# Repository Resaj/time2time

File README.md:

# time2time

Chronometer with partials measurement for the line-following competitions.

Characteristics:
- ESP32 module (STM microcontroller + Bluetooth + Wifi)
- Industrial distance sensor for robots pass-through detection
- Lipo 1S battery
- USB Lipo battery charge management
- I2C OLED display port
- Buzzer for robots pass-through signaling
- RGB led for chronometer status signaling
- Firmware upload via USB
- Address selection to synchronize several modules
- Expansion port for future improvements

This project has been motivated because of the limitations that the last chronometer had. The main purpose is to communicate the system with the PC of the competition organization and facilitate the taking and visualization of the times.

## Author

[Rubén Espino San José](https://github.com/Resaj)

## License

_All these products are released under [Creative Commons Attribution-NonCommercial-ShareAlike 4.0 International License](http://creativecommons.org/licenses/by-nc-sa/4.0/)._

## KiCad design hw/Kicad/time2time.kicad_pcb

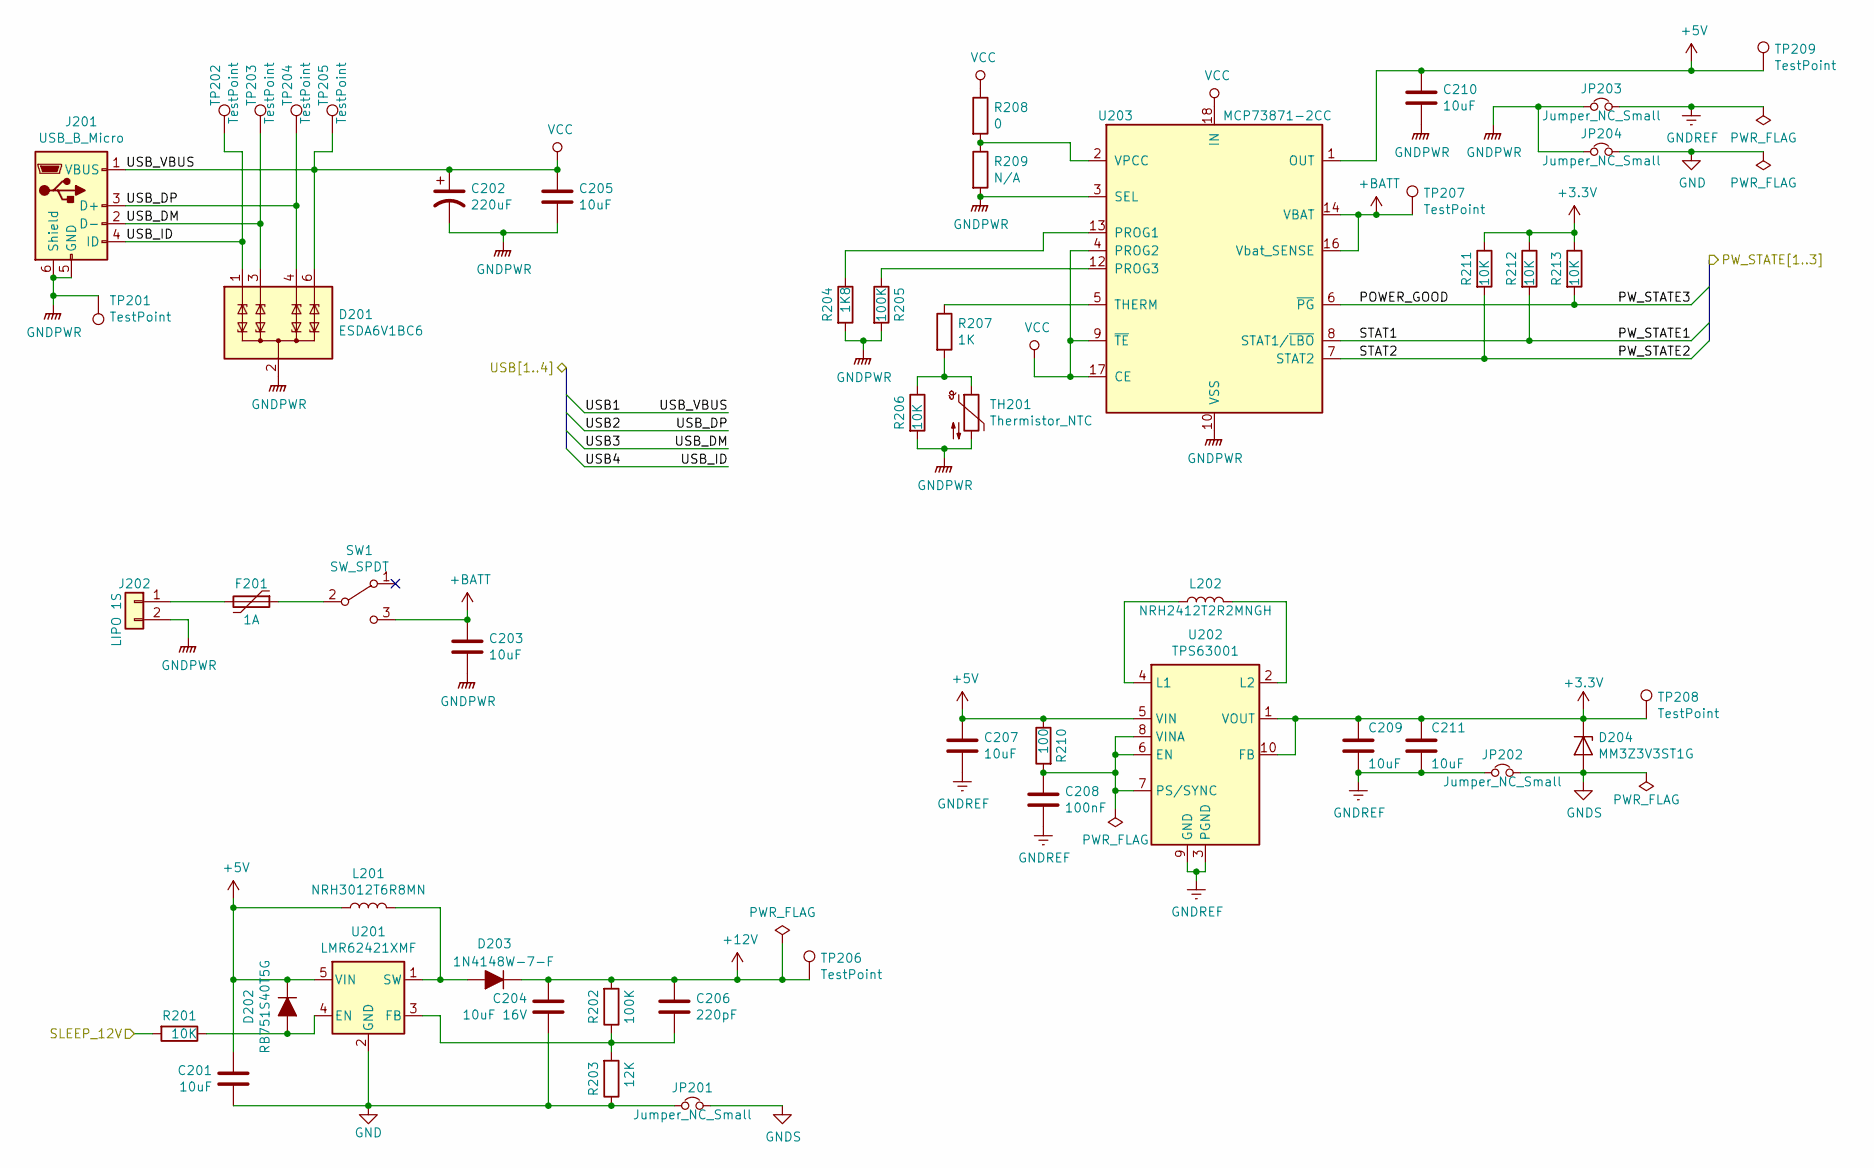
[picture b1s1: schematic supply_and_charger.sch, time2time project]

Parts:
C201, C203, C205, C207, C209, C210, C211: 10uF; C_0603_1608Metric
C202: 220uF; CP_Radial_D6.3mm_P2.50mm
C204: 10uF 16V; C_0603_1608Metric
C206: 220pF; C_0603_1608Metric
C208: 100nF; C_0603_1608Metric
D201: ESDA6V1BC6; SOT-23-6
D202: RB751S40T5G; D_SOD-523
D203: 1N4148W-7-F; D_SOD-123
D204: MM3Z3V3ST1G; D_SOD-323_HandSoldering
F201: 1A; Fuse_1812_4532Metric
J201: USB_B_Micro; USB_Micro-B_Molex-105017-0001
J202: LIPO 1S; JST_PH_B2B-PH-K_1x02_P2.00mm_Vertical
JP201, JP202, JP203, JP204: Jumper_NC_Small; SolderJumper-2_P1.3mm_Bridged_Pad1.0x1.5mm
L201: NRH3012T6R8MN; L_Taiyo-Yuden_NR-30xx_HandSoldering
L202: NRH2412T2R2MNGH; L_Taiyo-Yuden_NR-24xx_HandSoldering
R201, R206, R211, R212, R213: 10K; R_0603_1608Metric
R202, R205: 100K; R_0603_1608Metric
R203: 12K; R_0603_1608Metric
R204: 1K8; R_0603_1608Metric
R207: 1K; R_0603_1608Metric
R208: 0; R_0603_1608Metric
R209: N/A; R_0603_1608Metric
R210: 100; R_0603_1608Metric
SW1: SW_SPDT; SW_CuK_OS102011MA1QN1_SPDT_Angled
TH201: Thermistor_NTC; PinHeader_1x02_P2.54mm_Vertical
TP201, TP202, TP203, TP204, TP205, TP206, TP207, TP208, TP209: TestPoint; TestPoint_Pad_D1.5mm
U201: LMR62421XMF; SOT-23-5
U202: TPS63001; Texas_DRC0010J_ThermalVias
U203: MCP73871-2CC; QFN-20-1EP_4x4mm_P0.5mm_EP2.5x2.5mm

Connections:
+5V: C201.2, C207.1, C210.1, D202.1 (K), L201.1, R210.1, TP209.1, U201.5 (VIN), U202.5 (VIN), U203.1 (OUT), U203.20 (OUT); also elsewhere on the board
+12V: C204.2, C206.1, D203.1 (K), R202.2, TP206.1; also elsewhere on the board
+BATT: C203.1, SW1.3 (C), TP207.1, U203.14 (VBAT), U203.15 (VBAT), U203.16 (Vbat_SENSE); also elsewhere on the board
/microcontroller/PW_STATE1: R212.2, U203.8 (STAT1/~LBO~); also elsewhere on the board
/microcontroller/PW_STATE2: R211.2, U203.7 (STAT2); also elsewhere on the board
/microcontroller/SLEEP_12V: R201.2; also elsewhere on the board
/microcontroller/USB2: D201.4 (TVS3), J201.3 (D+), TP204.1; also elsewhere on the board
/microcontroller/USB3: D201.3 (TVS2), J201.2 (D-), TP203.1; also elsewhere on the board
/microcontroller/USB4: D201.1 (TVS1), J201.4 (ID), TP202.1
/supply & charger/POWER_GOOD: R213.2, U203.6 (~PG~); also elsewhere on the board
GND: C201.1, C204.1, JP201.1, JP204.2, R203.1, U201.2 (GND)
GNDPWR: C202.2, C203.2, C205.2, C210.2, D201.2 (COM), D201.5 (COM), J201.5 (GND), J201.6 (Shield), J202.2, JP203.1, JP204.1, R204.2, R205.2, R206.2, R209.2, TH201.2, TP201.1, U203.3 (SEL), U203.10 (VSS), U203.11 (VSS), U203.21 (VSS); also elsewhere on the board
GNDREF: C207.2, C208.2, C209.2, C211.2, JP202.1, JP203.2, U202.3 (PGND), U202.9 (GND), U202.11 (PGND)
GNDS: D204.2 (A), JP201.2, JP202.2; also elsewhere on the board
unnamed: C206.2, R202.1, R203.2, U201.3 (FB)
unnamed: C208.1, R210.2, U202.6 (EN), U202.7 (PS/SYNC), U202.8 (VINA)
unnamed: D202.2 (A), R201.1, U201.4 (EN)
unnamed: D203.2 (A), L201.2, U201.1 (SW)
unnamed: F201.1, SW1.2 (B)
unnamed: F201.2, J202.1
unnamed: L202.1, U202.4 (L1)
unnamed: L202.2, U202.2 (L2)
unnamed: R204.1, U203.13 (PROG1)
unnamed: R205.1, U203.12 (PROG3)
unnamed: R206.1, R207.2, TH201.1
unnamed: R207.1, U203.5 (THERM)
unnamed: R208.2, R209.1, U203.2 (VPCC)
VCC: C202.1, C205.1, D201.6 (TVS4), J201.1 (VBUS), R208.1, TP205.1, U203.4 (PROG2), U203.9 (~TE), U203.17 (CE), U203.18 (IN), U203.19 (IN); also elsewhere on the board

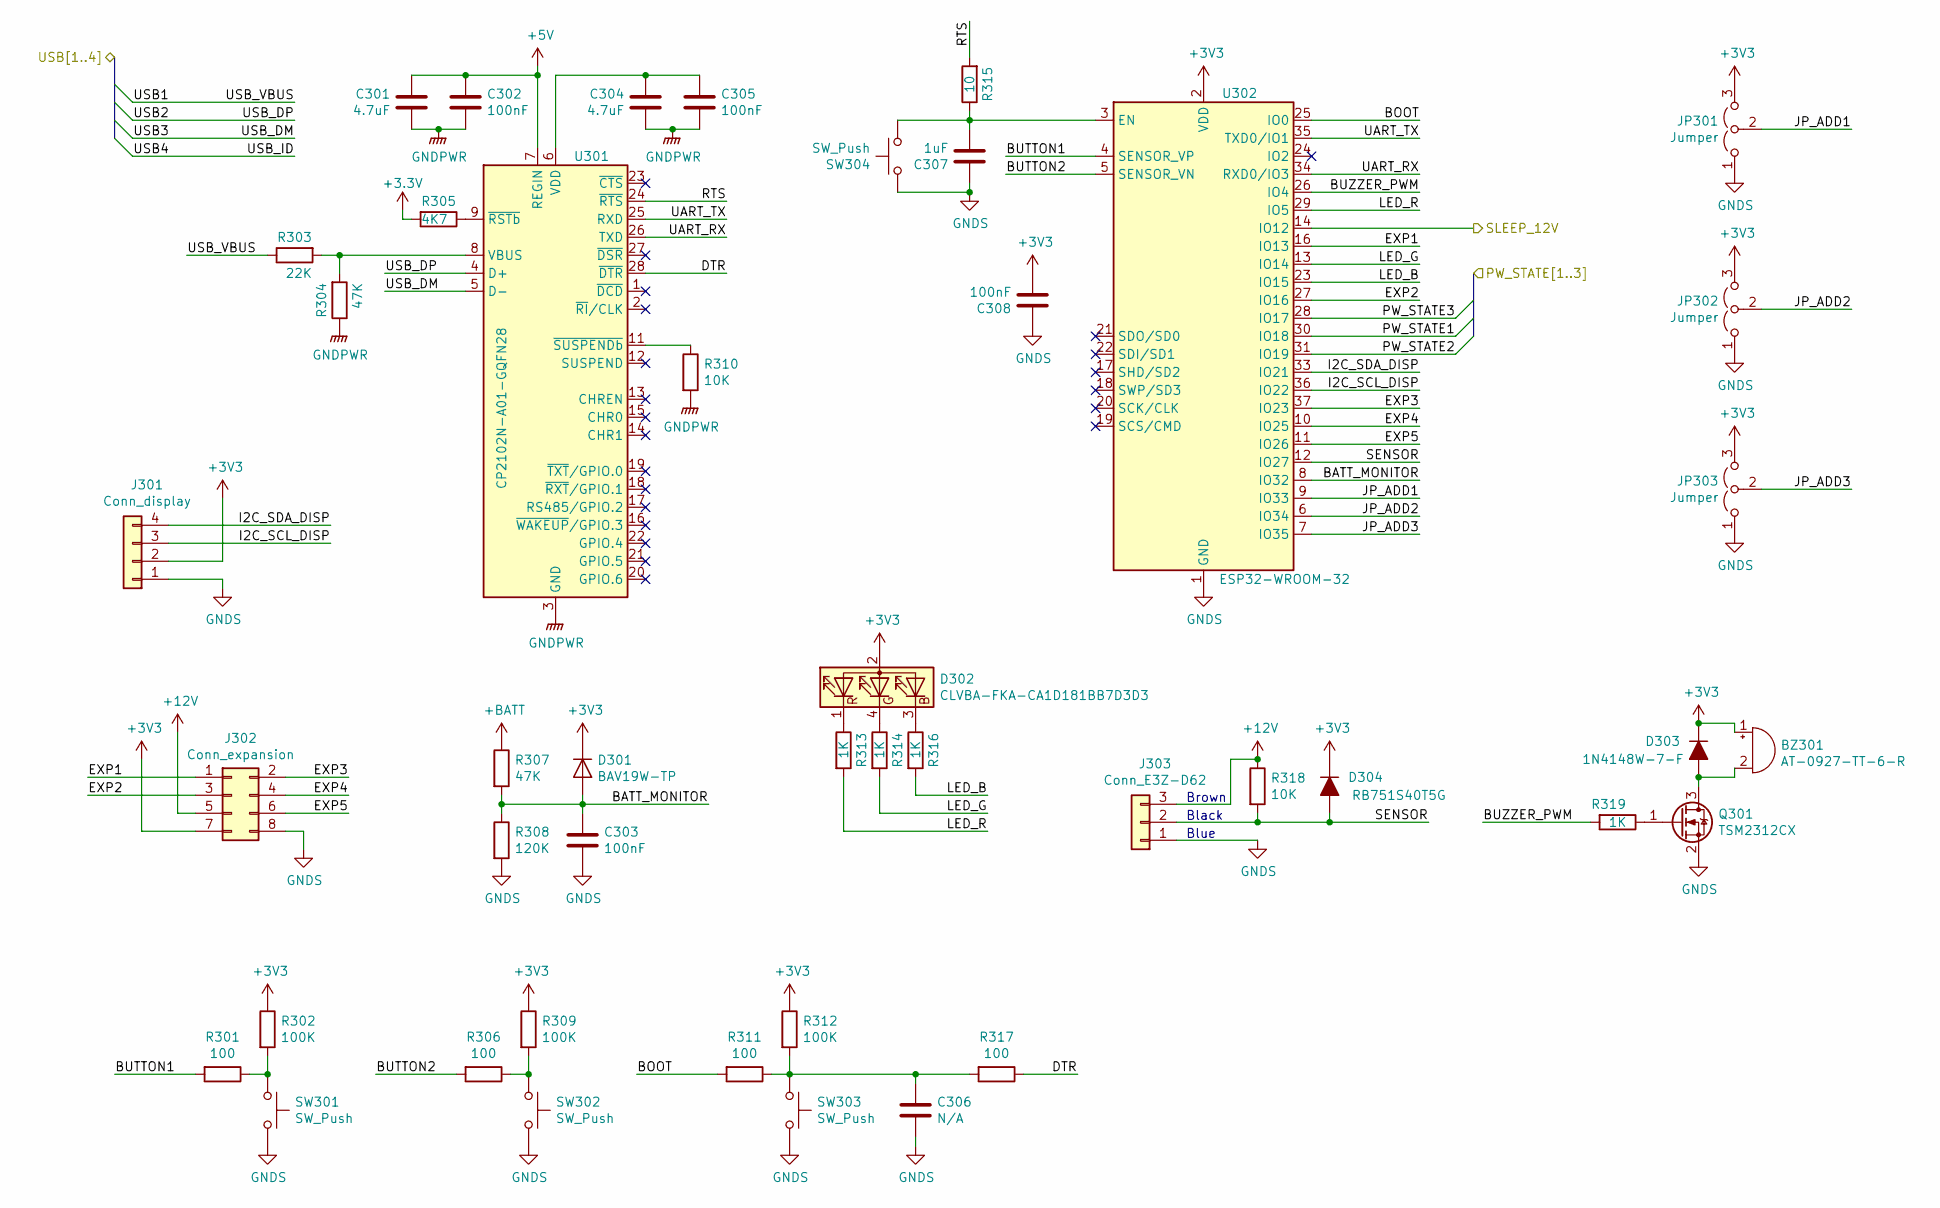
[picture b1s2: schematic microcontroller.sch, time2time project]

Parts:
BZ301: AT-0927-TT-6-R; MagneticBuzzer_PUI_AT-0927-TT-6-R
C301, C304: 4.7uF; C_0603_1608Metric
C302, C303, C305, C308: 100nF; C_0603_1608Metric
C306: N/A; C_0603_1608Metric
C307: 1uF; C_0603_1608Metric
D301: BAV19W-TP; D_SOD-123
D302: CLVBA-FKA-CA1D181BB7D3D3; LED_Cree-PLCC4_3.2x2.8mm_CCW
D303: 1N4148W-7-F; D_SOD-123
D304: RB751S40T5G; D_SOD-523
J301: Conn_display; PinSocket_1x04_P2.54mm_Vertical
J302: Conn_expansion; PinSocket_2x04_P2.54mm_Vertical
J303: Conn_E3Z-D62; PinSocket_1x03_P2.54mm_Vertical
JP301, JP302, JP303: Jumper; SolderJumper-3_P1.3mm_Open_Pad1.0x1.5mm
Q301: TSM2312CX; SOT-23
R301, R306, R311, R317: 100; R_0603_1608Metric
R302, R309, R312: 100K; R_0603_1608Metric
R303: 22K; R_0603_1608Metric
R304, R307: 47K; R_0603_1608Metric
R305: 4K7; R_0603_1608Metric
R308: 120K; R_0603_1608Metric
R310, R318: 10K; R_0603_1608Metric
R313, R314, R316, R319: 1K; R_0603_1608Metric
R315: 10; R_0603_1608Metric
SW301, SW302, SW303, SW304: SW_Push; SW_SPST_CK_RS282G05A3
U301: CP2102N-A01-GQFN28; QFN-28-1EP_5x5mm_P0.5mm_EP3.35x3.35mm
U302: ESP32-WROOM-32

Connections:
+5V: C301.1, C302.1, U301.7 (REGIN); also elsewhere on the board
+12V: J302.5, J303.3, R318.1; also elsewhere on the board
+BATT: R307.1; also elsewhere on the board
/microcontroller/BATT_MONITOR: C303.1, D301.2 (A), R307.2, R308.1, U302.8 (IO32)
/microcontroller/BOOT: R311.2, U302.25 (IO0)
/microcontroller/BUTTON1: R301.2, U302.4 (SENSOR_VP)
/microcontroller/BUTTON2: R306.2, U302.5 (SENSOR_VN)
/microcontroller/BUZZER_PWM: R319.2, U302.26 (IO4)
/microcontroller/DTR: R317.1, U301.28 (~DTR)
/microcontroller/EXP1: J302.1, U302.16 (IO13)
/microcontroller/EXP2: J302.3, U302.27 (IO16)
/microcontroller/EXP3: J302.2, U302.37 (IO23)
/microcontroller/EXP4: J302.4, U302.10 (IO25)
/microcontroller/EXP5: J302.6, U302.11 (IO26)
/microcontroller/I2C_SCL_DISP: J301.3, U302.36 (IO22)
/microcontroller/I2C_SDA_DISP: J301.4, U302.33 (IO21)
/microcontroller/JP_ADD1: JP301.2 (C), U302.9 (IO33)
/microcontroller/JP_ADD2: JP302.2 (C), U302.6 (IO34)
/microcontroller/JP_ADD3: JP303.2 (C), U302.7 (IO35)
/microcontroller/LED_B: R316.2, U302.23 (IO15)
/microcontroller/LED_G: R314.2, U302.13 (IO14)
/microcontroller/LED_R: R313.2, U302.29 (IO5)
/microcontroller/PW_STATE1: U302.30 (IO18); also elsewhere on the board
/microcontroller/PW_STATE2: U302.31 (IO19); also elsewhere on the board
/microcontroller/RTS: R315.2, U301.24 (~RTS)
/microcontroller/SENSOR: D304.2 (A), J303.2, R318.2, U302.12 (IO27)
/microcontroller/SLEEP_12V: U302.14 (IO12); also elsewhere on the board
/microcontroller/UART_RX: U301.26 (TXD), U302.34 (RXD0/IO3)
/microcontroller/UART_TX: U301.25 (RXD), U302.35 (TXD0/IO1)
/microcontroller/USB2: U301.4 (D+); also elsewhere on the board
/microcontroller/USB3: U301.5 (D-); also elsewhere on the board
/supply & charger/POWER_GOOD: U302.28 (IO17); also elsewhere on the board
GNDPWR: C301.2, C302.2, C304.2, C305.2, R304.1, R310.2, U301.3 (GND), U301.29 (GND); also elsewhere on the board
GNDS: C303.2, C306.2, C307.1, C308.1, J301.1, J302.8, J303.1, JP301.1 (A), JP302.1 (A), JP303.1 (A), Q301.2 (S), R308.2, SW301.2, SW302.2, SW303.2, SW304.1, U302.1 (GND), U302.15 (GND), U302.38 (GND), U302.39 (GND); also elsewhere on the board
unnamed: BZ301.2 (+), D303.2 (A), Q301.3 (D)
unnamed: C304.1, C305.1, U301.6 (VDD)
unnamed: C306.1, R311.1, R312.2, R317.2, SW303.1
unnamed: C307.2, R315.1, SW304.2, U302.3 (EN)
unnamed: D302.1 (RK), R313.1
unnamed: D302.3 (BK), R316.1
unnamed: D302.4 (GK), R314.1
unnamed: Q301.1 (G), R319.1
unnamed: R301.1, R302.2, SW301.1
unnamed: R303.2, R304.2, U301.8 (VBUS)
unnamed: R305.1, U301.9 (~RSTb)
unnamed: R306.1, R309.2, SW302.1
unnamed: R310.1, U301.11 (~SUSPENDb)
VCC: R303.1; also elsewhere on the board

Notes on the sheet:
Brown
Black
Blue

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
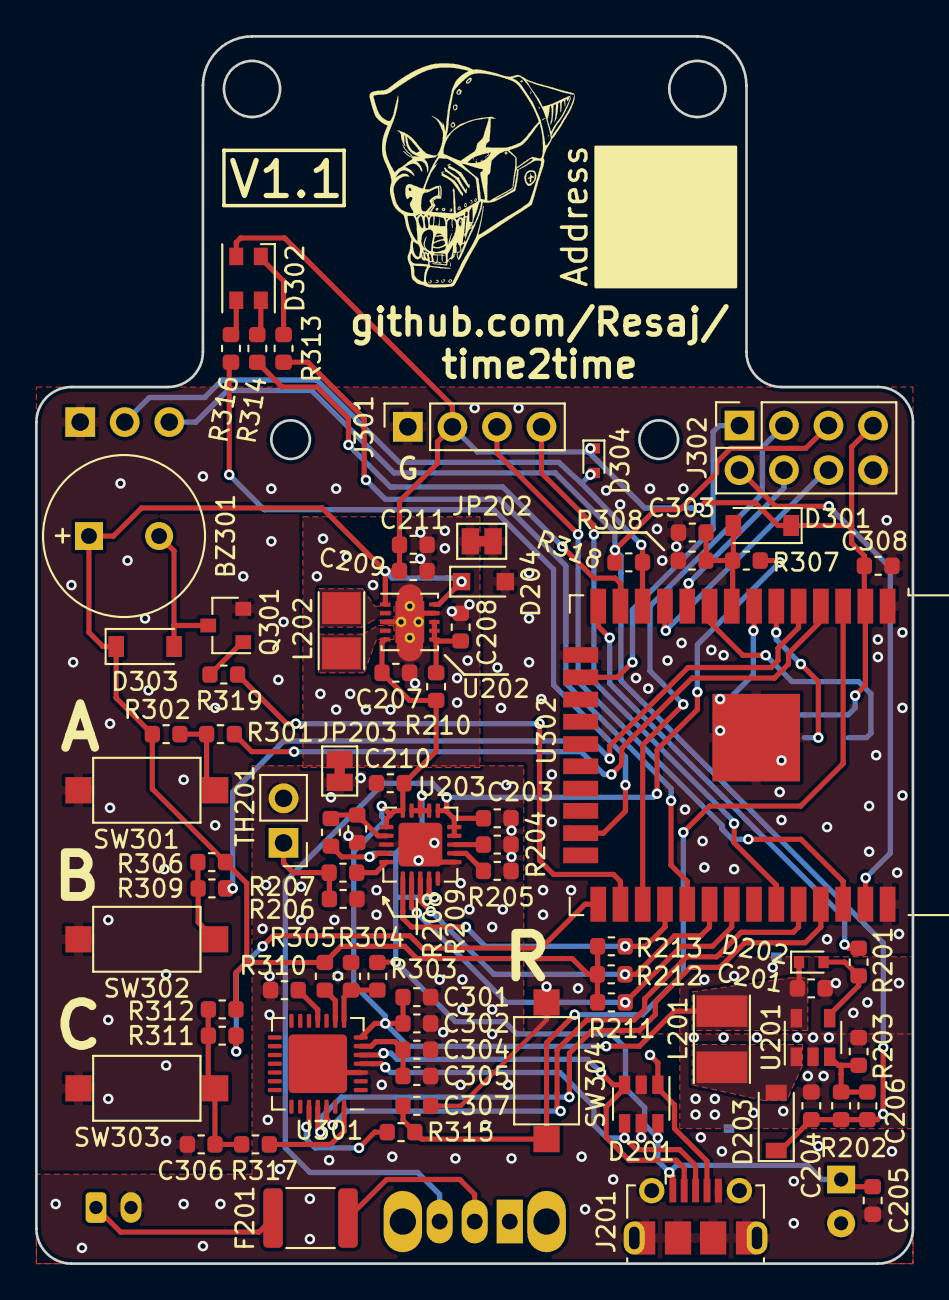
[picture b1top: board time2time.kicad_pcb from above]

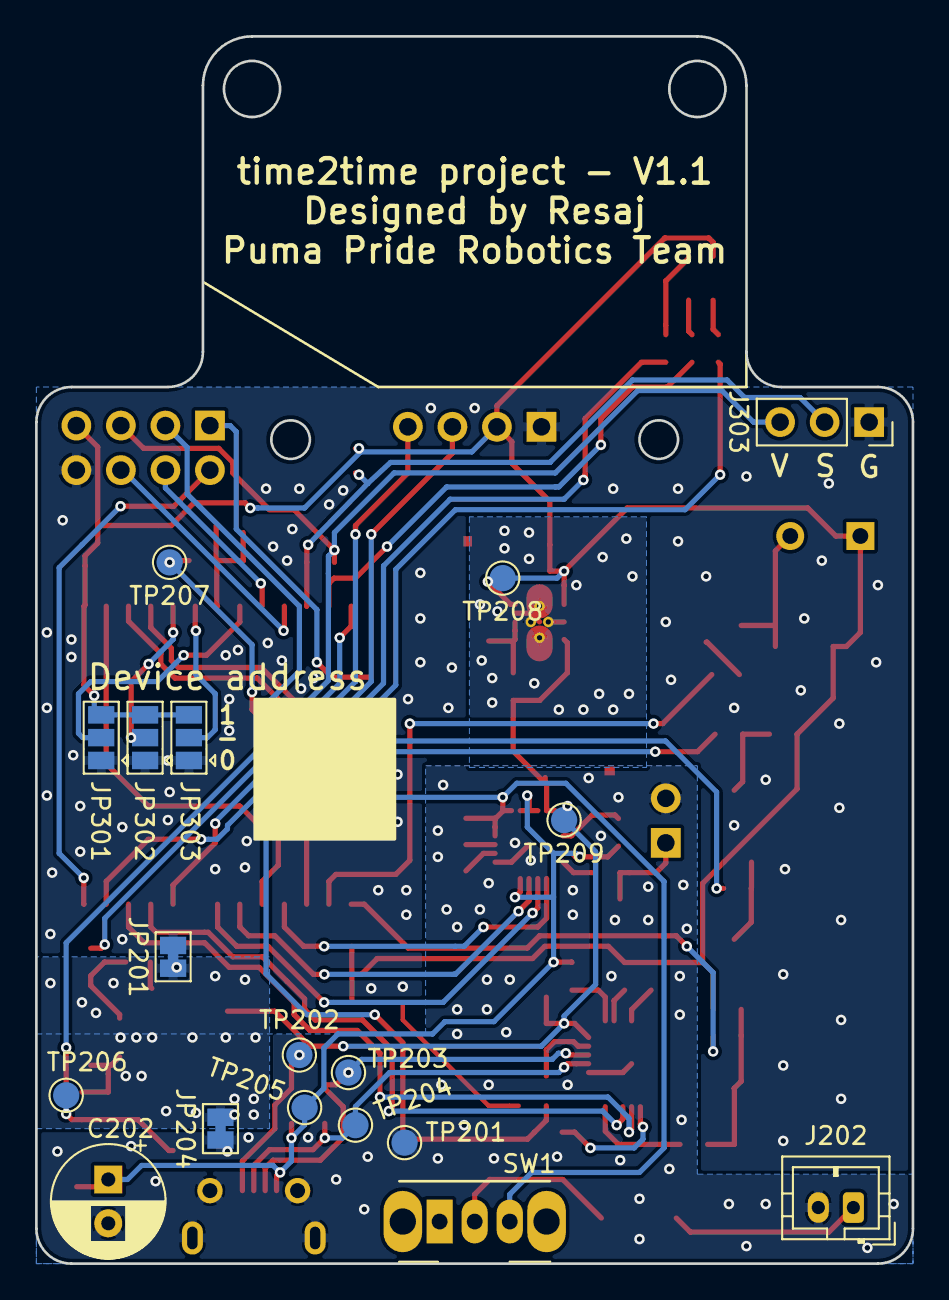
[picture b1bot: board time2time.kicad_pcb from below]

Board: 2 copper layers, 50.0 x 70.0 mm, 96 parts (18 on the bottom side), 65 nets.

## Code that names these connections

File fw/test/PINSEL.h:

#define UART_TX			1
#define UART_RX			3
#define BUZZER_PWM		4
#define LED_R			5
#define LED_G			14
#define LED_B			15
#define SLEEP_12V		12
#define EXP1			13
#define EXP2			16
#define EXP3			23
#define EXP4			25
#define EXP5			26
#define POWER_GOOD		17
#define STAT1			18
#define STAT2			19
#define I2C_SDA_DISP		21
#define I2C_SCL_DISP		22
#define SENSOR			27
#define BATT_MONITOR		32
#define JP_ADD1			33
#define JP_ADD2			34
#define JP_ADD3			35
#define BUTTON1			36
#define BUTTON2			39
#define BUTTON3      0

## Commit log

2019-09-24 First commit. PCB included
2019-09-24 Readme modified
2019-09-26 Pins modes specified in PINSEL
2019-10-29 V1.1 version. UART fixed and some signals renamed
2019-10-30 Resistor value changed for ADC battery monitor
2019-11-01 Test program added
2019-11-02 Some translations fixed
2019-11-03 3D casing added
2019-11-04 Basic chronometer firmware added
2019-11-05 Fixed some details of 3D casing
2019-11-06 Fixed sensor init
2019-11-08 Firmware multipurpose added
2019-12-01 Images added
2019-12-08 Image added
2020-04-25 Casing modified for raising the sensor and holding the PCB better
2020-05-31 Complete program renamed. Folder struct modified. Added some modules for peripheral control
2020-05-31 Added some peripheral modules
2020-06-07 Added buttons basic functions to the complete program. Changed names of pins.
2020-06-07 t2t_fw. Added pass sensor functionality
2020-06-13 t2t_fw. Changed some types
2020-06-13 t2t_fw. Buzzer library implemented
2020-06-14 t2t_fw. Display library modified and abstracted from main. Minor changes
2020-06-14 t2t_fw. 12v supply enable function modified
2020-06-24 t2t_fw. Added scheduler for controlling all the task. Added state machine module to control the chronometer modes
2020-06-24 t2t_fw. Minor changes on buzzer module
2020-06-24 t2t_fw. Buttons states filtered
2020-06-25 t2t_fw. Fixed errors for peripherals initialization and buttons functionament
2020-06-25 t2t_fw. Fixed state errors of buzzer module
2020-06-26 t2t_fw. Fixed errors of display module
2020-06-27 t2t_fw. Fixed errors of supply module
2020-06-27 t2t_fw. Fixed errors of state machine module
2020-06-27 t2t_fw. Minor changes
2020-06-29 t2t_fw. Scheduler added with timer interruption. Display period execution changed. Sensor interruption modified
2020-07-10 t2t_fw. Buzzer module modified. Added functionality to storage and manage buzzer tasks with a circular buffer
2020-07-11 t2t_fw. Added new buzzer functionality to x laps time mode. Saves best total time and do triple beep
2020-07-13 t2t_fw. Added transfer function to convert ADC value to battery voltage
2020-08-02 t2t_fw. Format changes and led task function renamed
2020-08-02 t2t_fw. RGB led module improvements added. Square, triangle and sinusoidal waves programmed
2020-08-02 t2t_fw. Added battery charger diagnostics and showed them through the led
2020-08-29 t2t_fw. Added number of laps selection for the x_laps_time_mode. Best time record variables shared between all modes
2020-09-12 t2t_fw. Variables format changed. Unnecessary TODO comments deleted
2020-11-01 t2t_fw. State machine adapted to any number of menu options. Minor changes.
2020-11-01 t2t_fw. Added functions to manage the sensor active edge
2020-11-01 t2t_fw. Toast mode added
2020-11-08 t2t.fw. Added init functions for ESP NOW
2020-11-15 test. Program modified to show MAC address. Minor changes
2020-11-15 test_ESPnow. Test added to check the communication between two nodes
2020-11-24 t2t_fw. Added message types and configured the link of the nodes for the ESP_now communication
2020-11-24 test_ESPnow. Minor changes. Configure message receive callback before linking the nodes
2020-11-29 t2t_fw. Added a new node address
2020-11-29 t2t_test. Rename the basic firmware test
2020-11-29 t2t_test_ESPnow. Rename the ESPnow test
2020-12-02 t2t_fw. Move the MAC address list to a new config file. Ignore the git syncronization of the personal MAC addresses. Create template to define the MAC addresses
2020-12-13 t2t_fw. Added ESPnow protocol documentation
2021-02-28 t2t_fw. MAC address list file renamed
2021-02-28 t2t_fw. Added new functionament modes and message types
2021-02-28 t2t_fw. Add schottky diode to prevent the ESP32 sensor pin from exced 3V3
2021-02-28 t2t_fw. Change the minimum hole size to 0.3 mm in the PCB design
2021-03-01 hw. PCB modified to compliant with the clearance of 6mil between tracks and vias
2021-03-28 manuals. Added first manuals in English and Spanish. Quick user guide and sensor adjustment
2021-08-11 test. Minor fixes
2021-08-11 t2t_fw. Add a new mode to show the information of the T2T node
2021-08-11 t2t_fw. Show the number of the page in the main menu
2021-08-11 t2t_fw. Show node addresses in the T2T information mode
2021-08-16 t2t_fw. Update ESPnow msg procotol. Add comments to the ESPnow module functions
2021-08-16 twt_fw. Fixed some details in the communication protocol
2021-08-16 t2t_fw. Fixed the checking of the MAC address
2021-08-17 t2t_fw. Fix MAC address checking
2021-08-17 t2t_fw. Show the linked nodes in the info menu
2021-08-18 t2t_test_ESPnow. Fix updating of the sensor detection to avoid send messages constantly
2021-08-18 t2t_fw. Initialyze peerInfo to fix the linking between the nodes
2021-08-18 t2t_fw. Create espnow_task function
2021-08-26 t2t_fw. Sleep mode to charge the battery faster. Simplify the calling of the functions of the modes
2022-01-15 t2t_fw. Enable deep sleep mode with 12V sensor disabling
2022-01-20 t2t_fw. Link messages communication done
2022-01-21 t2t_fw. Send link messages periodicaly to maintain the communication alive
2022-01-22 t2t_fw. Add functionality for the battery message. Fix and simplify the detection of the number of nodes
2022-01-22 t2t_fw. Turn time variable to local. Create a function to get it from other modules
2022-01-23 t2t_now. Unify link and sync msg type to simplify the communication. Save ESP tx and rx times to have a time control over the communication
2022-01-23 t2t_fw. Simplify linking communication
2022-01-24 t2t_fw. Adapt the mode messages protocol to manage the requests, acceptances and rejections. Prepare mode messages reception to be processed by the state machine
2022-01-30 t2t_fw. Add some functionality for the multi-node modes. Add function declarations in all the modules
2022-02-01 t2t_fw. Simplify the dependencies between ESPnow and state machine modules
2022-02-06 t2t_mode. Change mode message management to make it easier. Extract link message management to another function
2022-02-09 t2t_fw. Fix linking and communication recovery while the nodes return from the working modes. Exit from the working mode while any of the working nodes is not linked
2022-02-12 t2t_fw. Fix functionality about exit from the modes when a linking error on any working node happends
2022-02-15 t2t_fw. Test tx time with an example code. Modify the behaviour of the link messages tx while working to avoid sending several
2022-02-15 t2t_fw. Clean the code for the tx time testing
2022-03-10 t2t_fw. Fix led synchronization between nodes in a working mode
2022-04-05 t2t_fw. Finish start/stop mode. Manage sensor detections and messages for detections and times to show
2022-04-05 t2t_fw. Change stop beep to be made by the secondary node in the start/stop mode
2022-04-06 t2t_mode. Change the name of "start/stop" to "time trial" mode. Create the "start/stop" mode with an active start
2022-04-13 t2t_fw. Add the firmware version to the t2t information panel
2022-06-02 manuals. Add the manual for uplading the firmware. Rename some names of the manuals
2022-06-05 manuals. Add tutorial 4 with the working modes

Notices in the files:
hw/Kicad/microcontroller.sch:
CC BY-NC-SA license
